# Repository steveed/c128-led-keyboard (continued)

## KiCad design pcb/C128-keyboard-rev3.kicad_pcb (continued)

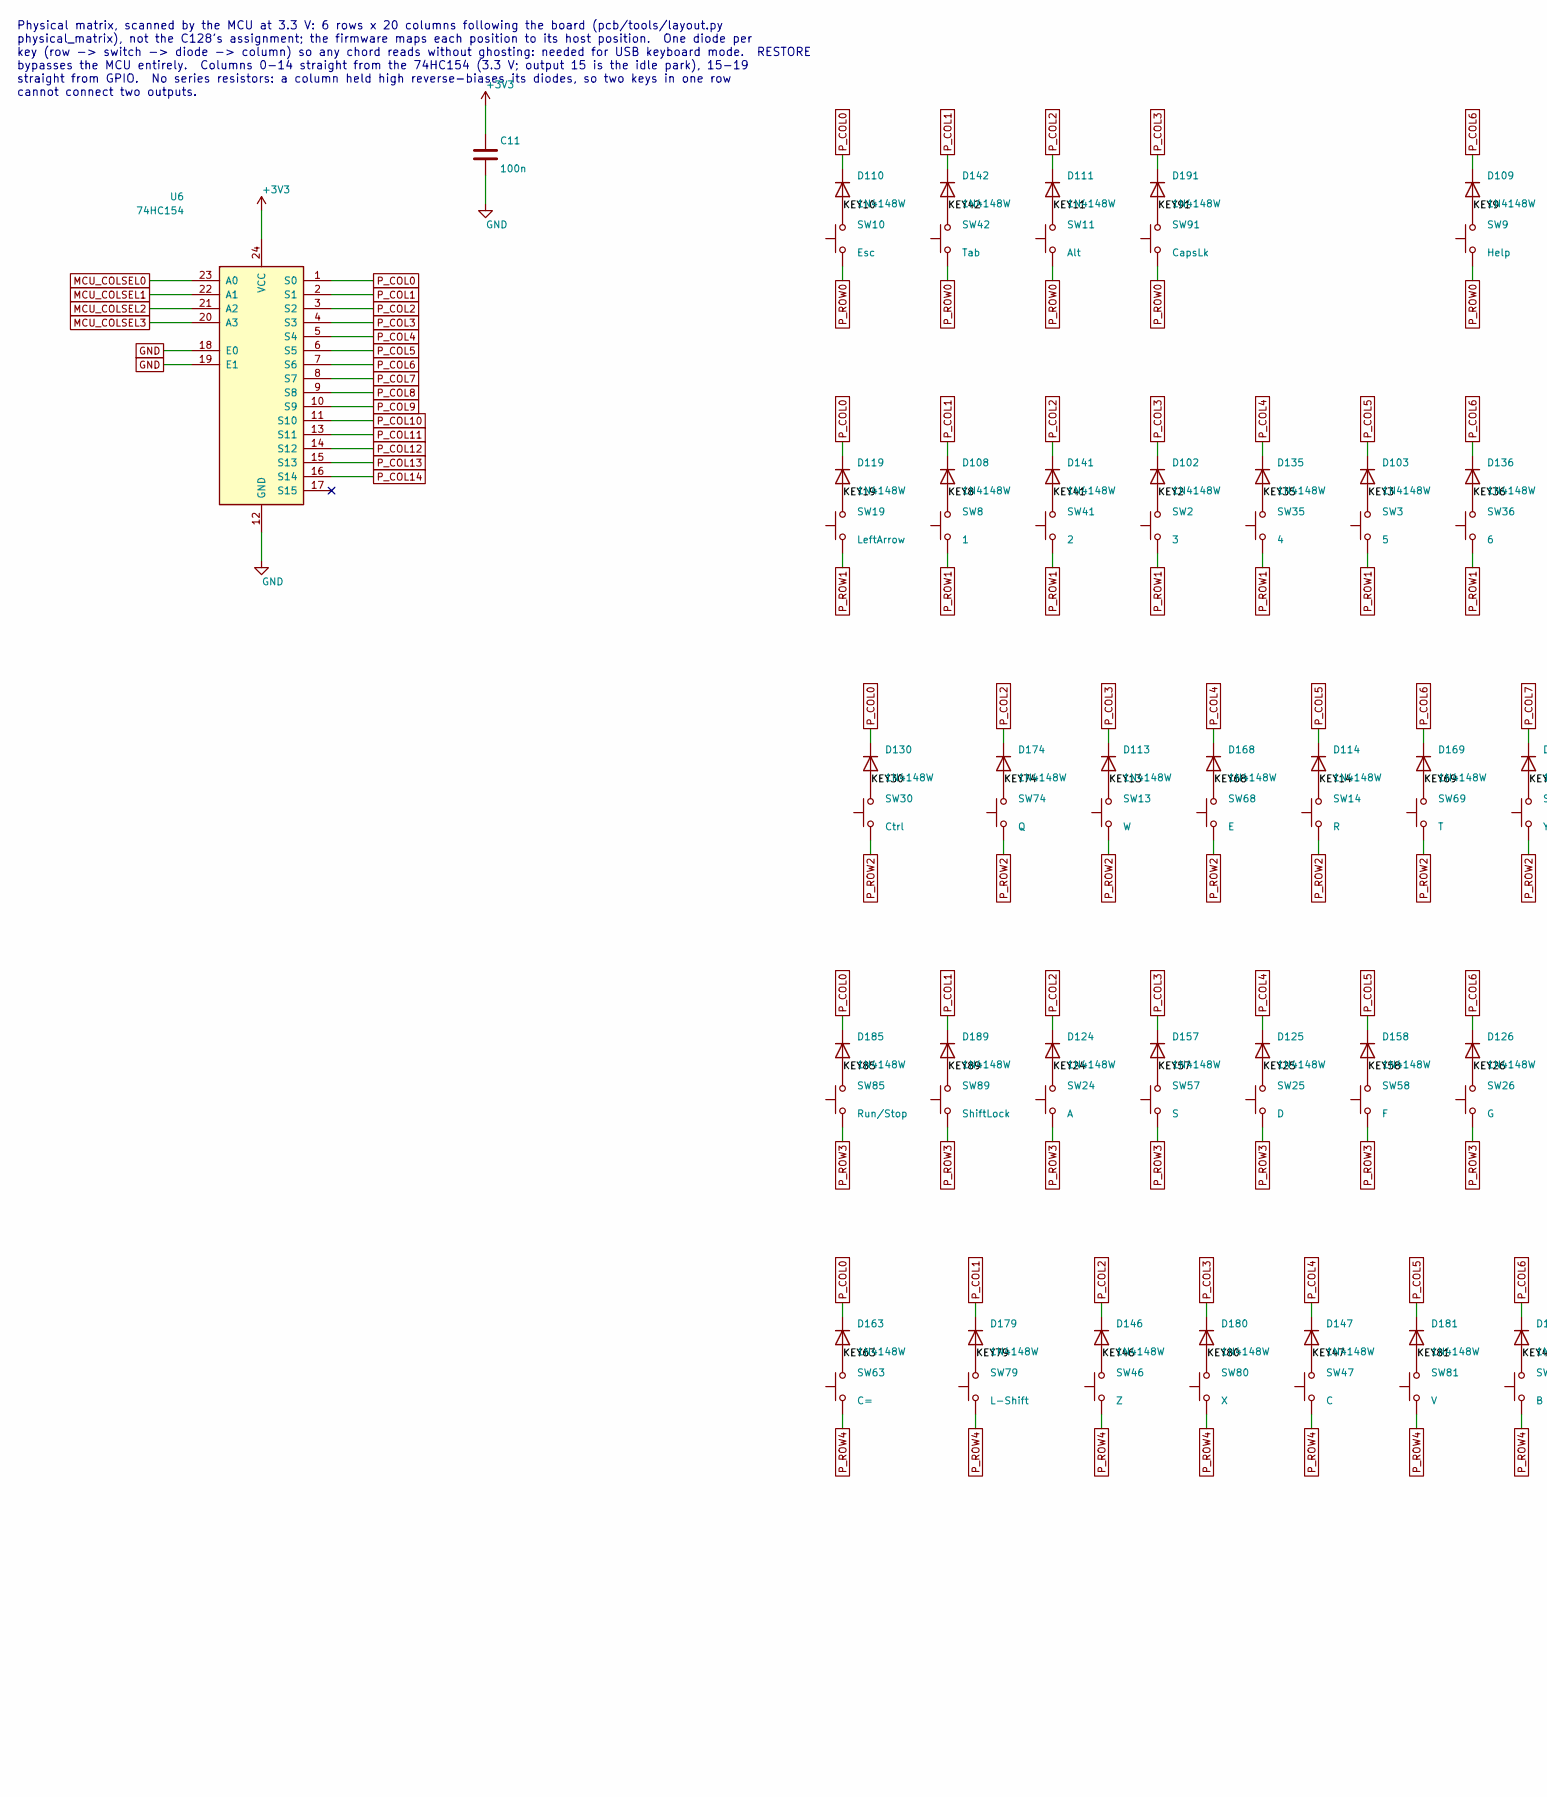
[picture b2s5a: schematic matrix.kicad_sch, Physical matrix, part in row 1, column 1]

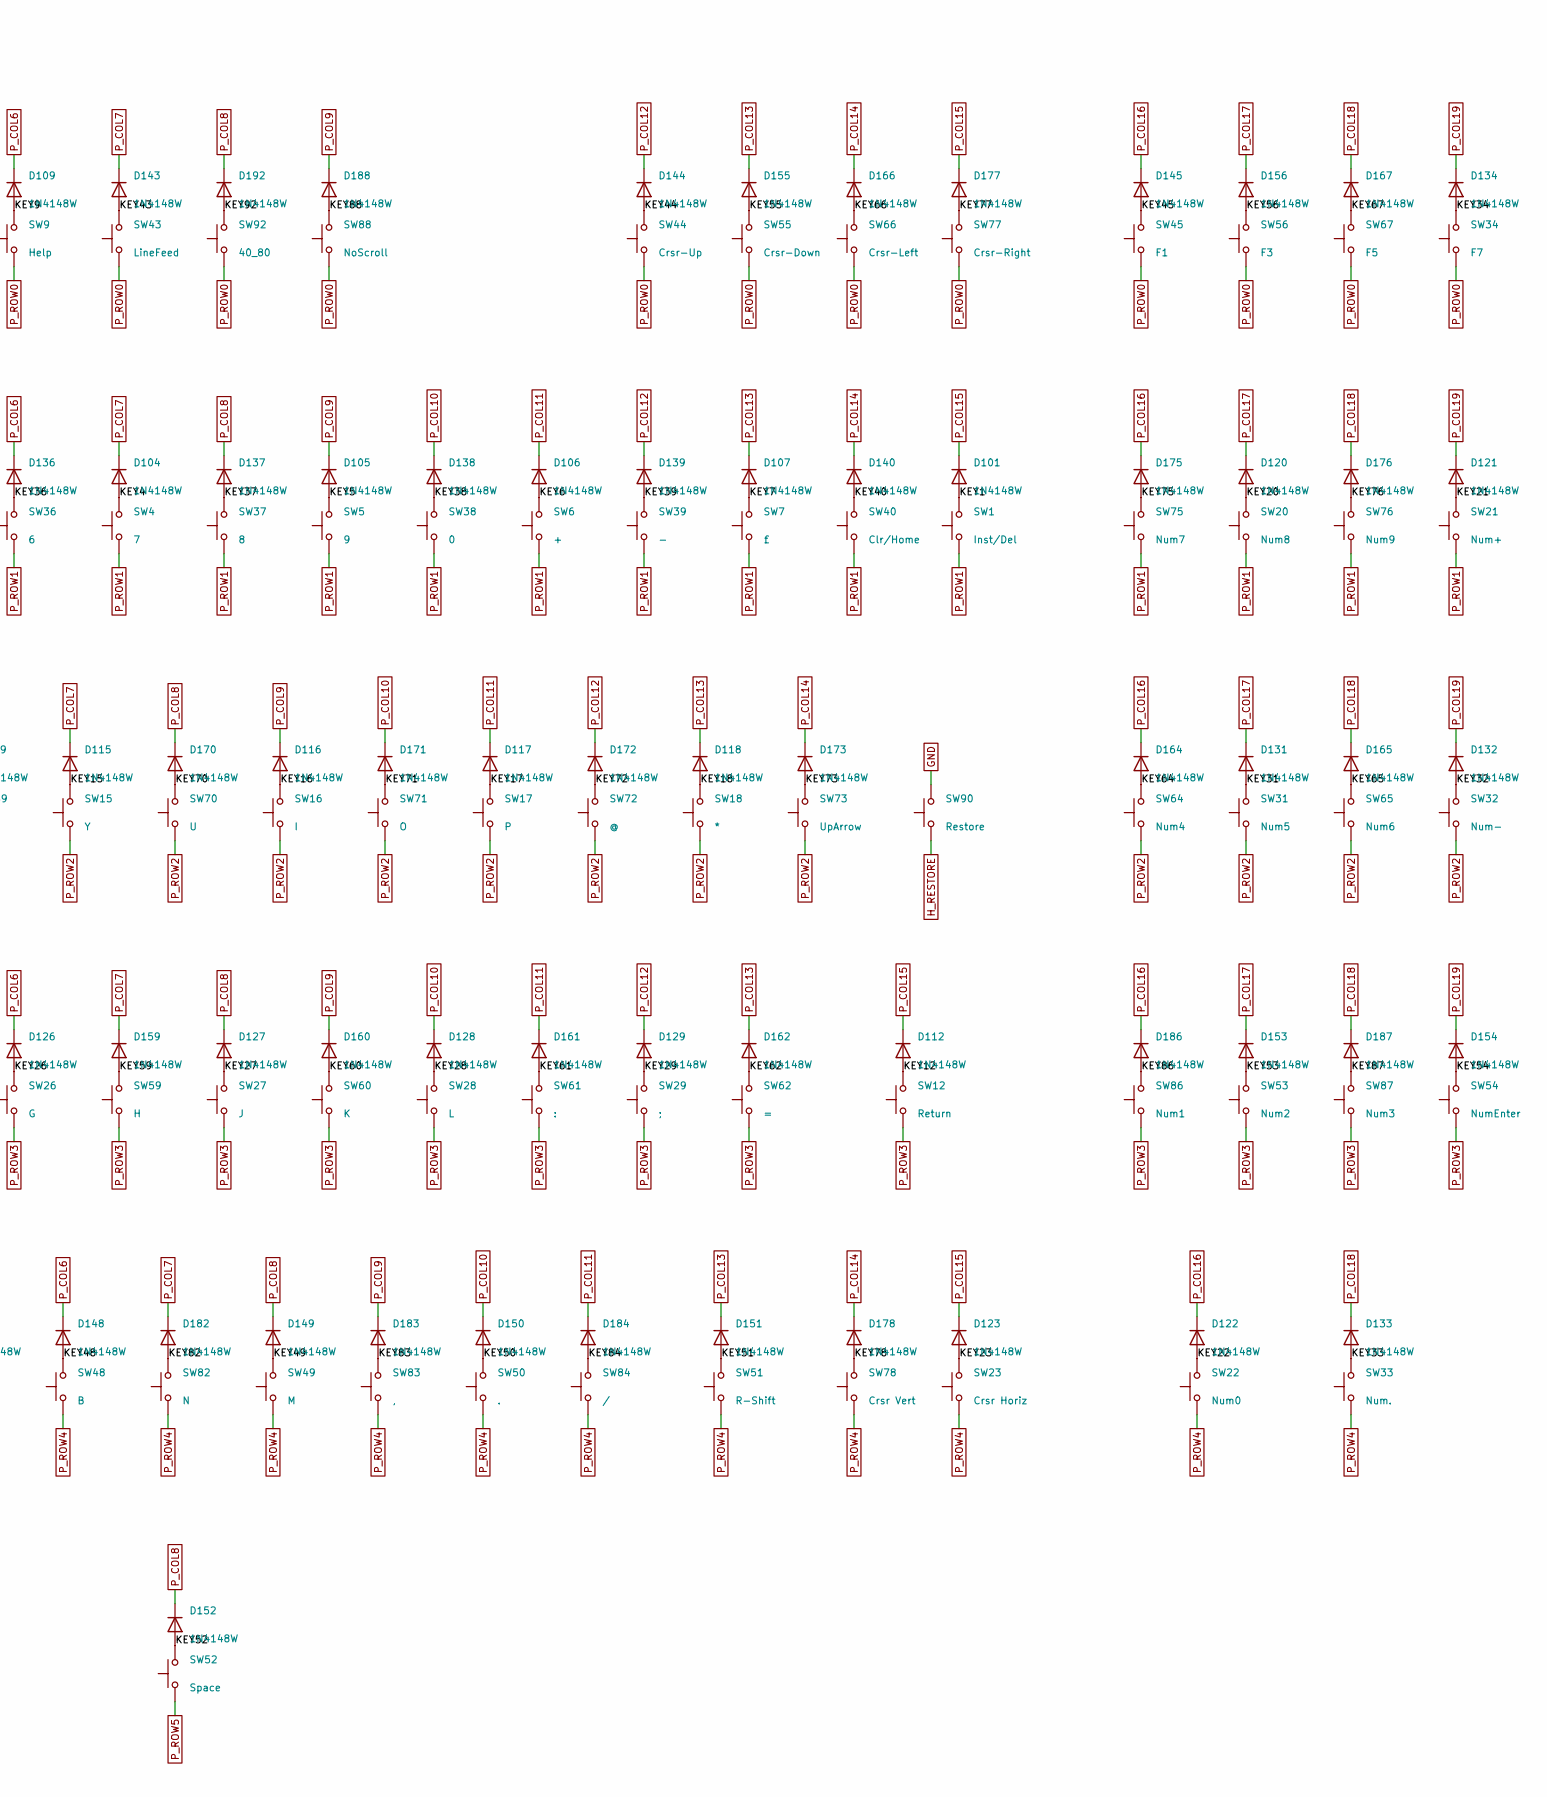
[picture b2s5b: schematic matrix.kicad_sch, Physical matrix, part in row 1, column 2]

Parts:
C11: 100n; C_0603_1608Metric_Pad1.08x0.95mm_HandSolder; LCSC C14663
D101, D102, D103, D104, D105, D106, D107, D108, D109, D110, D111, D112, D113, D114, D115, D116, D117, D118, D119, D120, D121, D122, D123, D124, D125, D126, D127, D128, D129, D130, D131, D132, D133, D134, D135, D136, D137, D138, D139, D140, D141, D142, D143, D144, D145, D146, D147, D148, D149, D150, D151, D152, D153, D154, D155, D156, D157, D158, D159, D160, D161, D162, D163, D164, D165, D166, D167, D168, D169, D170, D171, D172, D173, D174, D175, D176, D177, D178, D179, D180, D181, D182, D183, D184, D185, D186, D187, D188, D189, D191, D192: 1N4148W; D_SOD-123; LCSC C81598
SW1: Inst/Del; SW_MX_1u
SW2: 3; SW_MX_1u
SW3: 5; SW_MX_1u
SW4: 7; SW_MX_1u
SW5: 9; SW_MX_1u
SW6: +; SW_MX_1u
SW7: £; SW_MX_1u
SW8: 1; SW_MX_1u
SW9: Help; SW_MX_1u
SW10: Esc; SW_MX_1u
SW11: Alt; SW_MX_1u
SW12: Return; SW_MX_2u
SW13: W; SW_MX_1u
SW14: R; SW_MX_1u
SW15: Y; SW_MX_1u
SW16: I; SW_MX_1u
SW17: P; SW_MX_1u
SW18: *; SW_MX_1u
SW19: LeftArrow; SW_MX_1u
SW20: Num8; SW_MX_1u
SW21: Num+; SW_MX_1u
SW22: Num0; SW_MX_2u
SW23: Crsr Horiz; SW_MX_1u
SW24: A; SW_MX_1u
SW25: D; SW_MX_1u
SW26: G; SW_MX_1u
SW27: J; SW_MX_1u
SW28: L; SW_MX_1u
SW29: ;; SW_MX_1u
SW30: Ctrl; SW_MX_1u
SW31: Num5; SW_MX_1u
SW32: Num-; SW_MX_1u
SW33: Num.; SW_MX_1u
SW34: F7; SW_MX_1u
SW35: 4; SW_MX_1u
SW36: 6; SW_MX_1u
SW37: 8; SW_MX_1u
SW38: 0; SW_MX_1u
SW39: -; SW_MX_1u
SW40: Clr/Home; SW_MX_1u
SW41: 2; SW_MX_1u
SW42: Tab; SW_MX_1u
SW43: LineFeed; SW_MX_1u
SW44: Crsr-Up; SW_MX_1u
SW45: F1; SW_MX_1u
SW46: Z; SW_MX_1u
SW47: C; SW_MX_1u
SW48: B; SW_MX_1u
SW49: M; SW_MX_1u
SW50: .; SW_MX_1u
SW51: R-Shift; SW_MX_1u
SW52: Space; SW_MX_Spacebar
SW53: Num2; SW_MX_1u
SW54: NumEnter; SW_MX_2u
SW55: Crsr-Down; SW_MX_1u
SW56: F3; SW_MX_1u
SW57: S; SW_MX_1u
SW58: F; SW_MX_1u
SW59: H; SW_MX_1u
SW60: K; SW_MX_1u
SW61: :; SW_MX_1u
SW62: =; SW_MX_1u
SW63: C=; SW_MX_1u
SW64: Num4; SW_MX_1u
SW65: Num6; SW_MX_1u
SW66: Crsr-Left; SW_MX_1u
SW67: F5; SW_MX_1u
SW68: E; SW_MX_1u
SW69: T; SW_MX_1u
SW70: U; SW_MX_1u
SW71: O; SW_MX_1u
SW72: @; SW_MX_1u
SW73: UpArrow; SW_MX_1u
SW74: Q; SW_MX_1u
SW75: Num7; SW_MX_1u
SW76: Num9; SW_MX_1u
SW77: Crsr-Right; SW_MX_1u
SW78: Crsr Vert; SW_MX_1u
SW79: L-Shift; SW_MX_1.5u
SW80: X; SW_MX_1u
SW81: V; SW_MX_1u
SW82: N; SW_MX_1u
SW83: ,; SW_MX_1u
SW84: /; SW_MX_1u
SW85: Run/Stop; SW_MX_1u
SW86: Num1; SW_MX_1u
SW87: Num3; SW_MX_1u
SW88: NoScroll; SW_MX_1u
SW89: ShiftLock; SW_MX_1u
SW90: Restore; SW_MX_1.5u
SW91: CapsLk; SW_MX_1u
SW92: 40_80; SW_MX_1u
U6: 74HC154; SOIC-24W_7.5x15.4mm_P1.27mm; LCSC C2832236

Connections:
+3V3: C11.1, U6.24 (VCC); also elsewhere on the board
/Physical matrix/KEY1: D101.2 (A), SW1.2
/Physical matrix/KEY2: D102.2 (A), SW2.2
/Physical matrix/KEY3: D103.2 (A), SW3.2
/Physical matrix/KEY4: D104.2 (A), SW4.2
/Physical matrix/KEY5: D105.2 (A), SW5.2
/Physical matrix/KEY6: D106.2 (A), SW6.2
/Physical matrix/KEY7: D107.2 (A), SW7.2
/Physical matrix/KEY8: D108.2 (A), SW8.2
/Physical matrix/KEY9: D109.2 (A), SW9.2
/Physical matrix/KEY10: D110.2 (A), SW10.2
/Physical matrix/KEY11: D111.2 (A), SW11.2
/Physical matrix/KEY12: D112.2 (A), SW12.2
/Physical matrix/KEY13: D113.2 (A), SW13.2
/Physical matrix/KEY14: D114.2 (A), SW14.2
/Physical matrix/KEY15: D115.2 (A), SW15.2
/Physical matrix/KEY16: D116.2 (A), SW16.2
/Physical matrix/KEY17: D117.2 (A), SW17.2
/Physical matrix/KEY18: D118.2 (A), SW18.2
/Physical matrix/KEY19: D119.2 (A), SW19.2
/Physical matrix/KEY20: D120.2 (A), SW20.2
/Physical matrix/KEY21: D121.2 (A), SW21.2
/Physical matrix/KEY22: D122.2 (A), SW22.2
/Physical matrix/KEY23: D123.2 (A), SW23.2
/Physical matrix/KEY24: D124.2 (A), SW24.2
/Physical matrix/KEY25: D125.2 (A), SW25.2
/Physical matrix/KEY26: D126.2 (A), SW26.2
/Physical matrix/KEY27: D127.2 (A), SW27.2
/Physical matrix/KEY28: D128.2 (A), SW28.2
/Physical matrix/KEY29: D129.2 (A), SW29.2
/Physical matrix/KEY30: D130.2 (A), SW30.2
/Physical matrix/KEY31: D131.2 (A), SW31.2
/Physical matrix/KEY32: D132.2 (A), SW32.2
/Physical matrix/KEY33: D133.2 (A), SW33.2
/Physical matrix/KEY34: D134.2 (A), SW34.2
/Physical matrix/KEY35: D135.2 (A), SW35.2
/Physical matrix/KEY36: D136.2 (A), SW36.2
/Physical matrix/KEY37: D137.2 (A), SW37.2
/Physical matrix/KEY38: D138.2 (A), SW38.2
/Physical matrix/KEY39: D139.2 (A), SW39.2
/Physical matrix/KEY40: D140.2 (A), SW40.2
/Physical matrix/KEY41: D141.2 (A), SW41.2
/Physical matrix/KEY42: D142.2 (A), SW42.2
/Physical matrix/KEY43: D143.2 (A), SW43.2
/Physical matrix/KEY44: D144.2 (A), SW44.2
/Physical matrix/KEY45: D145.2 (A), SW45.2
/Physical matrix/KEY46: D146.2 (A), SW46.2
/Physical matrix/KEY47: D147.2 (A), SW47.2
/Physical matrix/KEY48: D148.2 (A), SW48.2
/Physical matrix/KEY49: D149.2 (A), SW49.2
/Physical matrix/KEY50: D150.2 (A), SW50.2
/Physical matrix/KEY51: D151.2 (A), SW51.2
/Physical matrix/KEY52: D152.2 (A), SW52.2
/Physical matrix/KEY53: D153.2 (A), SW53.2
/Physical matrix/KEY54: D154.2 (A), SW54.2
/Physical matrix/KEY55: D155.2 (A), SW55.2
/Physical matrix/KEY56: D156.2 (A), SW56.2
/Physical matrix/KEY57: D157.2 (A), SW57.2
/Physical matrix/KEY58: D158.2 (A), SW58.2
/Physical matrix/KEY59: D159.2 (A), SW59.2
/Physical matrix/KEY60: D160.2 (A), SW60.2
/Physical matrix/KEY61: D161.2 (A), SW61.2
/Physical matrix/KEY62: D162.2 (A), SW62.2
/Physical matrix/KEY63: D163.2 (A), SW63.2
/Physical matrix/KEY64: D164.2 (A), SW64.2
/Physical matrix/KEY65: D165.2 (A), SW65.2
/Physical matrix/KEY66: D166.2 (A), SW66.2
/Physical matrix/KEY67: D167.2 (A), SW67.2
/Physical matrix/KEY68: D168.2 (A), SW68.2
/Physical matrix/KEY69: D169.2 (A), SW69.2
/Physical matrix/KEY70: D170.2 (A), SW70.2
/Physical matrix/KEY71: D171.2 (A), SW71.2
/Physical matrix/KEY72: D172.2 (A), SW72.2
/Physical matrix/KEY73: D173.2 (A), SW73.2
/Physical matrix/KEY74: D174.2 (A), SW74.2
/Physical matrix/KEY75: D175.2 (A), SW75.2
/Physical matrix/KEY76: D176.2 (A), SW76.2
/Physical matrix/KEY77: D177.2 (A), SW77.2
/Physical matrix/KEY78: D178.2 (A), SW78.2
/Physical matrix/KEY79: D179.2 (A), SW79.2
/Physical matrix/KEY80: D180.2 (A), SW80.2
/Physical matrix/KEY81: D181.2 (A), SW81.2
/Physical matrix/KEY82: D182.2 (A), SW82.2
/Physical matrix/KEY83: D183.2 (A), SW83.2
/Physical matrix/KEY84: D184.2 (A), SW84.2
/Physical matrix/KEY85: D185.2 (A), SW85.2
/Physical matrix/KEY86: D186.2 (A), SW86.2
/Physical matrix/KEY87: D187.2 (A), SW87.2
/Physical matrix/KEY88: D188.2 (A), SW88.2
/Physical matrix/KEY89: D189.2 (A), SW89.2
/Physical matrix/KEY91: D191.2 (A), SW91.2
/Physical matrix/KEY92: D192.2 (A), SW92.2
GND: C11.2, SW90.2, U6.12 (GND), U6.18 (E0), U6.19 (E1); also elsewhere on the board
H_RESTORE: SW90.1; also elsewhere on the board
MCU_COLSEL0: U6.23 (A0); also elsewhere on the board
MCU_COLSEL1: U6.22 (A1); also elsewhere on the board
MCU_COLSEL2: U6.21 (A2); also elsewhere on the board
MCU_COLSEL3: U6.20 (A3); also elsewhere on the board
P_COL0: D110.1 (K), D119.1 (K), D130.1 (K), D163.1 (K), D185.1 (K), U6.1 (S0)
P_COL1: D108.1 (K), D142.1 (K), D179.1 (K), D189.1 (K), U6.2 (S1)
P_COL2: D111.1 (K), D124.1 (K), D141.1 (K), D146.1 (K), D174.1 (K), U6.3 (S2)
P_COL3: D102.1 (K), D113.1 (K), D157.1 (K), D180.1 (K), D191.1 (K), U6.4 (S3)
P_COL4: D125.1 (K), D135.1 (K), D147.1 (K), D168.1 (K), U6.5 (S4)
P_COL5: D103.1 (K), D114.1 (K), D158.1 (K), D181.1 (K), U6.6 (S5)
P_COL6: D109.1 (K), D126.1 (K), D136.1 (K), D148.1 (K), D169.1 (K), U6.7 (S6)
P_COL7: D104.1 (K), D115.1 (K), D143.1 (K), D159.1 (K), D182.1 (K), U6.8 (S7)
P_COL8: D127.1 (K), D137.1 (K), D149.1 (K), D152.1 (K), D170.1 (K), D192.1 (K), U6.9 (S8)
P_COL9: D105.1 (K), D116.1 (K), D160.1 (K), D183.1 (K), D188.1 (K), U6.10 (S9)
P_COL10: D128.1 (K), D138.1 (K), D150.1 (K), D171.1 (K), U6.11 (S10)
P_COL11: D106.1 (K), D117.1 (K), D161.1 (K), D184.1 (K), U6.13 (S11)
P_COL12: D129.1 (K), D139.1 (K), D144.1 (K), D172.1 (K), U6.14 (S12)
P_COL13: D107.1 (K), D118.1 (K), D151.1 (K), D155.1 (K), D162.1 (K), U6.15 (S13)
P_COL14: D140.1 (K), D166.1 (K), D173.1 (K), D178.1 (K), U6.16 (S14)
P_COL15: D101.1 (K), D112.1 (K), D123.1 (K), D177.1 (K); also elsewhere on the board
P_COL16: D122.1 (K), D145.1 (K), D164.1 (K), D175.1 (K), D186.1 (K); also elsewhere on the board
P_COL17: D120.1 (K), D131.1 (K), D153.1 (K), D156.1 (K); also elsewhere on the board
P_COL18: D133.1 (K), D165.1 (K), D167.1 (K), D176.1 (K), D187.1 (K); also elsewhere on the board
P_COL19: D121.1 (K), D132.1 (K), D134.1 (K), D154.1 (K); also elsewhere on the board
P_ROW0: SW9.1, SW10.1, SW11.1, SW34.1, SW42.1, SW43.1, SW44.1, SW45.1, SW55.1, SW56.1, SW66.1, SW67.1, SW77.1, SW88.1, SW91.1, SW92.1; also elsewhere on the board
P_ROW1: SW1.1, SW2.1, SW3.1, SW4.1, SW5.1, SW6.1, SW7.1, SW8.1, SW19.1, SW20.1, SW21.1, SW35.1, SW36.1, SW37.1, SW38.1, SW39.1, SW40.1, SW41.1, SW75.1, SW76.1; also elsewhere on the board
P_ROW2: SW13.1, SW14.1, SW15.1, SW16.1, SW17.1, SW18.1, SW30.1, SW31.1, SW32.1, SW64.1, SW65.1, SW68.1, SW69.1, SW70.1, SW71.1, SW72.1, SW73.1, SW74.1; also elsewhere on the board
P_ROW3: SW12.1, SW24.1, SW25.1, SW26.1, SW27.1, SW28.1, SW29.1, SW53.1, SW54.1, SW57.1, SW58.1, SW59.1, SW60.1, SW61.1, SW62.1, SW85.1, SW86.1, SW87.1, SW89.1; also elsewhere on the board
P_ROW4: SW22.1, SW23.1, SW33.1, SW46.1, SW47.1, SW48.1, SW49.1, SW50.1, SW51.1, SW63.1, SW78.1, SW79.1, SW80.1, SW81.1, SW82.1, SW83.1, SW84.1; also elsewhere on the board
P_ROW5: SW52.1; also elsewhere on the board

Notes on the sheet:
Physical matrix, scanned by the MCU at 3.3 V: 6 rows x 20 columns following the board (pcb/tools/layout.py physical_matrix), not the C128's assignment; the firmware maps each position to its host position. One diode per key (row -> switch -> diode -> column) so any chord reads without ghosting: nee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

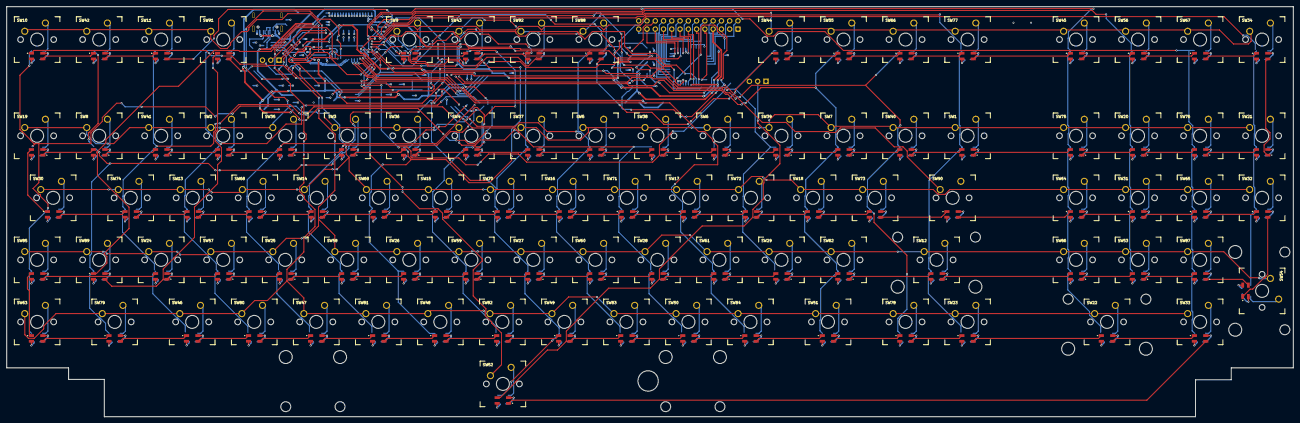
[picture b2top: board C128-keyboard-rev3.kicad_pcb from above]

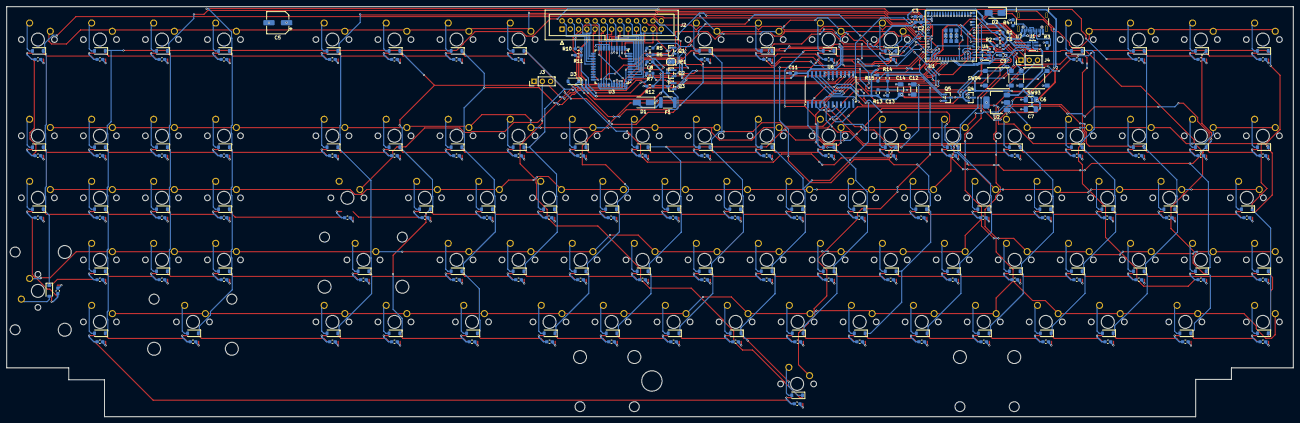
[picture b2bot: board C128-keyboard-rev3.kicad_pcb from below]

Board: 4 copper layers, 395.2 x 125.9 mm, 414 parts (230 on the bottom side), 266 nets.

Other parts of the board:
C12, C14: 10u; C_1206_3216Metric_Pad1.33x1.80mm_HandSolder
C13: 220n; C_0603_1608Metric_Pad1.08x0.95mm_HandSolder
Q4: AO3401A; SOT-23
Q5: 2N7002; SOT-23
R13, R15: 100k; R_0603_1608Metric_Pad0.98x0.95mm_HandSolder
R14: 10k; R_0603_1608Metric_Pad0.98x0.95mm_HandSolder

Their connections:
GND: C12.2, C14.2, Q5.2 (S), R15.2; also elsewhere on the board
LED_PWR_GATE: C13.2, Q4.1 (G), R13.2, R14.1
LED_PWR_PULL: Q5.3 (D), R14.2
MCU_LED_EN: Q5.1 (G), R15.1; also elsewhere on the board

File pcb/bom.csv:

"Reference","Value","Footprint","LCSC","QUANTITY"
"C1,C2,C8,C9,C11,C101-C192","100n","Capacitor_SMD:C_0603_1608Metric_Pad1.08x0.95mm_HandSolder","C14663","97"
"C3","10u","Capacitor_SMD:C_0603_1608Metric_Pad1.08x0.95mm_HandSolder","C19702","1"
"C5","220u","Capacitor_SMD:CP_Elec_6.3x7.7","C125979","1"
"C6,C7","10u","Capacitor_SMD:C_1206_3216Metric_Pad1.33x1.80mm_HandSolder","C13585","2"
"D1,D2","SS34","Diode_SMD:D_SMA","C8678","2"
"D3,D101-D189,D191,D192","1N4148W","Diode_SMD:D_SOD-123","C81598","92"
"F1","1.1A","Fuse:Fuse_1812_4532Metric","C142746","1"
"J1","USB-C","c128rev3:USB_C_Receptacle_ShouHan_TYPE-C-16P-3MD-040","C41417453","1"
"J2","C128 keyboard (D-sub IDC order)","Connector_IDC:IDC-Header_2x13_P2.54mm_Vertical","","1"
"J3","Ext LED","Connector_PinHeader_2.54mm:PinHeader_1x03_P2.54mm_Vertical","","1"
"J4","UART0","Connector_PinHeader_2.54mm:PinHeader_1x03_P2.54mm_Vertical","","1"
"JP1","80col default","Jumper:SolderJumper-2_P1.3mm_Open_RoundedPad1.0x1.5mm","","1"
"LED1-LED92","SK6812MINI","c128rev3:LED_SK6812MINI_MX","C2886570","92"
"Q1-Q3","2N7002","Package_TO_SOT_SMD:SOT-23","C8545","3"
"R1,R2,R6,R10,R11","10k","Resistor_SMD:R_0603_1608Metric_Pad0.98x0.95mm_HandSolder","C25804","5"
"R3,R4","5k1","Resistor_SMD:R_0603_1608Metric_Pad0.98x0.95mm_HandSolder","C23186","2"
"R5,R7,R12","100k","Resistor_SMD:R_0603_1608Metric_Pad0.98x0.95mm_HandSolder","C25803","3"
"SW1","Inst/Del","c128rev3:SW_MX_1u","","1"
"SW2","3","c128rev3:SW_MX_1u","","1"
"SW3","5","c128rev3:SW_MX_1u","","1"
"SW4","7","c128rev3:SW_MX_1u","","1"
"SW5","9","c128rev3:SW_MX_1u","","1"
"SW6","+","c128rev3:SW_MX_1u","","1"
"SW7","£","c128rev3:SW_MX_1u","","1"
"SW8","1","c128rev3:SW_MX_1u","","1"
"SW9","Help","c128rev3:SW_MX_1u","","1"
"SW10","Esc","c128rev3:SW_MX_1u","","1"
"SW11","Alt","c128rev3:SW_MX_1u","","1"
"SW12","Return","c128rev3:SW_MX_2u","","1"
"SW13","W","c128rev3:SW_MX_1u","","1"
"SW14","R","c128rev3:SW_MX_1u","","1"
"SW15","Y","c128rev3:SW_MX_1u","","1"
"SW16","I","c128rev3:SW_MX_1u","","1"
"SW17","P","c128rev3:SW_MX_1u","","1"
"SW18","*","c128rev3:SW_MX_1u","","1"
"SW19","LeftArrow","c128rev3:SW_MX_1u","","1"
"SW20","Num8","c128rev3:SW_MX_1u","","1"
"SW21","Num+","c128rev3:SW_MX_1u","","1"
"SW22","Num0","c128rev3:SW_MX_2u","","1"
"SW23","Crsr Horiz","c128rev3:SW_MX_1u","","1"
"SW24","A","c128rev3:SW_MX_1u","","1"
"SW25","D","c128rev3:SW_MX_1u","","1"
"SW26","G","c128rev3:SW_MX_1u","","1"
"SW27","J","c128rev3:SW_MX_1u","","1"
"SW28","L","c128rev3:SW_MX_1u","","1"
"SW29",";","c128rev3:SW_MX_1u","","1"
"SW30","Ctrl","c128rev3:SW_MX_1u","","1"
"SW31","Num5","c128rev3:SW_MX_1u","","1"
"SW32","Num-","c128rev3:SW_MX_1u","","1"
"SW33","Num.","c128rev3:SW_MX_1u","","1"
"SW34","F7","c128rev3:SW_MX_1u","","1"
"SW35","4","c128rev3:SW_MX_1u","","1"
"SW36","6","c128rev3:SW_MX_1u","","1"
"SW37","8","c128rev3:SW_MX_1u","","1"
"SW38","0","c128rev3:SW_MX_1u","","1"
"SW39","-","c128rev3:SW_MX_1u","","1"
"SW40","Clr/Home","c128rev3:SW_MX_1u","","1"
"SW41","2","c128rev3:SW_MX_1u","","1"
"SW42","Tab","c128rev3:SW_MX_1u","","1"
"SW43","LineFeed","c128rev3:SW_MX_1u","","1"
"SW44","Crsr-Up","c128rev3:SW_MX_1u","","1"
"SW45","F1","c128rev3:SW_MX_1u","","1"
"SW46","Z","c128rev3:SW_MX_1u","","1"
"SW47","C","c128rev3:SW_MX_1u","","1"
"SW48","B","c128rev3:SW_MX_1u","","1"
"SW49","M","c128rev3:SW_MX_1u","","1"
"SW50",".","c128rev3:SW_MX_1u","","1"
"SW51","R-Shift","c128rev3:SW_MX_1u","","1"
"SW52","Space","c128rev3:SW_MX_Spacebar","","1"
"SW53","Num2","c128rev3:SW_MX_1u","","1"
"SW54","NumEnter","c128rev3:SW_MX_2u","","1"
"SW55","Crsr-Down","c128rev3:SW_MX_1u","","1"
"SW56","F3","c128rev3:SW_MX_1u","","1"
"SW57","S","c128rev3:SW_MX_1u","","1"
"SW58","F","c128rev3:SW_MX_1u","","1"
"SW59","H","c128rev3:SW_MX_1u","","1"
"SW60","K","c128rev3:SW_MX_1u","","1"
"SW61",":","c128rev3:SW_MX_1u","","1"
"SW62","=","c128rev3:SW_MX_1u","","1"
"SW63","C=","c128rev3:SW_MX_1u","","1"
"SW64","Num4","c128rev3:SW_MX_1u","","1"
"SW65","Num6","c128rev3:SW_MX_1u","","1"
"SW66","Crsr-Left","c128rev3:SW_MX_1u","","1"
"SW67","F5","c128rev3:SW_MX_1u","","1"
"SW68","E","c128rev3:SW_MX_1u","","1"
"SW69","T","c128rev3:SW_MX_1u","","1"
"SW70","U","c128rev3:SW_MX_1u","","1"
"SW71","O","c128rev3:SW_MX_1u","","1"
"SW72","@","c128rev3:SW_MX_1u","","1"
"SW73","UpArrow","c128rev3:SW_MX_1u","","1"
"SW74","Q","c128rev3:SW_MX_1u","","1"
"SW75","Num7","c128rev3:SW_MX_1u","","1"
"SW76","Num9","c128rev3:SW_MX_1u","","1"
"SW77","Crsr-Right","c128rev3:SW_MX_1u","","1"
"SW78","Crsr Vert","c128rev3:SW_MX_1u","","1"
"SW79","L-Shift","c128rev3:SW_MX_1.5u","","1"
"SW80","X","c128rev3:SW_MX_1u","","1"
"SW81","V","c128rev3:SW_MX_1u","","1"
"SW82","N","c128rev3:SW_MX_1u","","1"
"SW83",",","c128rev3:SW_MX_1u","","1"
"SW84","/","c128rev3:SW_MX_1u","","1"
"SW85","Run/Stop","c128rev3:SW_MX_1u","","1"
"SW86","Num1","c128rev3:SW_MX_1u","","1"
"SW87","Num3","c128rev3:SW_MX_1u","","1"
"SW88","NoScroll","c128rev3:SW_MX_1u","","1"
"SW89","ShiftLock","c128rev3:SW_MX_1u","","1"
"SW90","Restore","c128rev3:SW_MX_1.5u","","1"
"SW91","CapsLk","c128rev3:SW_MX_1u","","1"
"SW92","40_80","c128rev3:SW_MX_1u","","1"
"SW93","RESET","Button_Switch_SMD:SW_SPST_PTS645Sx43SMTR92","C221880","1"
"SW94","BOOT","Button_Switch_SMD:SW_SPST_PTS645Sx43SMTR92","C221880","1"
"U1","ESP32-S3-MINI-1U-N8","RF_Module:ESP32-S2-MINI-1U","C2980299","1"
"U2","AP7361C-33E","Package_TO_SOT_SMD:SOT-223-3_TabPin2","C500795","1"
"U3","CH446Q","Package_QFP:LQFP-44_10x10mm_P0.8mm","C109471","1"
"U4","74AHCT1G125","Package_TO_SOT_SMD:SOT-23-5","C7484","1"
"U6","74HC154","Package_SO:SOIC-24W_7.5x15.4mm_P1.27mm","C2832236","1"
"U7","USBLC6-2SC6","Package_TO_SOT_SMD:SOT-23-6","C7519","1"

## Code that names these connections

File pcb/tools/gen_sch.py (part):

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    # debug UART header
    j4 = sh.symbol("Connector_Generic:Conn_01x03", "J4", "UART0", (190, 60),
                   footprint="Connector_PinHeader_2.54mm:PinHeader_1x03_P2.54mm_Vertical")
    sh.connect(j4, 1, "MCU_TXD0"); sh.connect(j4, 2, "MCU_RXD0"); sh.connect(j4, 3, "GND", kind="label")

    # USB-C
    j1 = sh.symbol("Connector:USB_C_Receptacle_USB2.0_16P", "J1", "USB-C", (260, 120),
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            jp = sh.symbol("Jumper:SolderJumper_2_Open", "JP1", "80col default", (node[0], node[1] - 27.94), rot=90,
                           footprint="Jumper:SolderJumper-2_P1.3mm_Open_RoundedPad1.0x1.5mm")
            sh.path(jp.pin_end(1)[0], ru.pin_end(1)[0])   # pin 1 is the lower pad after rot 90
            sh.label("JP1_B", (node[0], node[1] - 16.51), rot=90)
            sh.connect(jp, 2, "+3V3")
        sh.junction(node)
        sh.wire(node, (node[0] - 7.62, node[1])); sh.glabel(gate_net, (node[0] - 7.62, node[1]), "L")
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            "Fit an IDC box header, or solder the ribbon straight into the pads on a flat.", (200, 268), 1.27)
    j3 = sh.symbol("Connector_Generic:Conn_01x03", "J3", "Ext LED", (330, 150),
                   footprint="Connector_PinHeader_2.54mm:PinHeader_1x03_P2.54mm_Vertical")
    sh.connect(j3, 1, "+5V_LED"); sh.connect(j3, 2, "LED_OUT"); sh.connect(j3, 3, "GND", kind="label")


def build_matrix(sh, switches):
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                       fields={"Key": s["val"]})
        if s["val"] == "Restore":
            # hard-wired to the host NMI line, no diode: it must work with the firmware dead
            sh.connect(sw, 1, "H_RESTORE", stub=2.54, kind="label")
            sh.connect(sw, 2, "GND", stub=2.54, kind="label")
            continue
        pr, pc = phys[s["ref"]]
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        din, _ = led.pin_end(3)
        dout, _ = led.pin_end(1)
        if i == 0:
            sh.wire(din, (din[0] - 5.08, din[1])); sh.glabel("LED_DATA_5V", (din[0] - 5.08, din[1]), "L")
        elif c == 0:
            sh.wire(din, (din[0] - 5.08, din[1])); sh.glabel(f"LED_D{i}", (din[0] - 5.08, din[1]), "L")
        else:
            sh.wire(prev_out, din)
            sh.label(f"LED_D{i}", ((prev_out[0] + din[0]) / 2 - 3.81, din[1]))
        if i == len(chain) - 1:
            sh.wire(dout, (dout[0] + 5.08, dout[1])); sh.glabel("LED_OUT", (dout[0] + 5.08, dout[1]), "R")
        elif c == per_row - 1:
            sh.wire(dout, (dout[0] + 5.08, dout[1])); sh.glabel(f"LED_D{i + 1}", (dout[0] + 5.08, dout[1]), "R")
        prev_out = dout
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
